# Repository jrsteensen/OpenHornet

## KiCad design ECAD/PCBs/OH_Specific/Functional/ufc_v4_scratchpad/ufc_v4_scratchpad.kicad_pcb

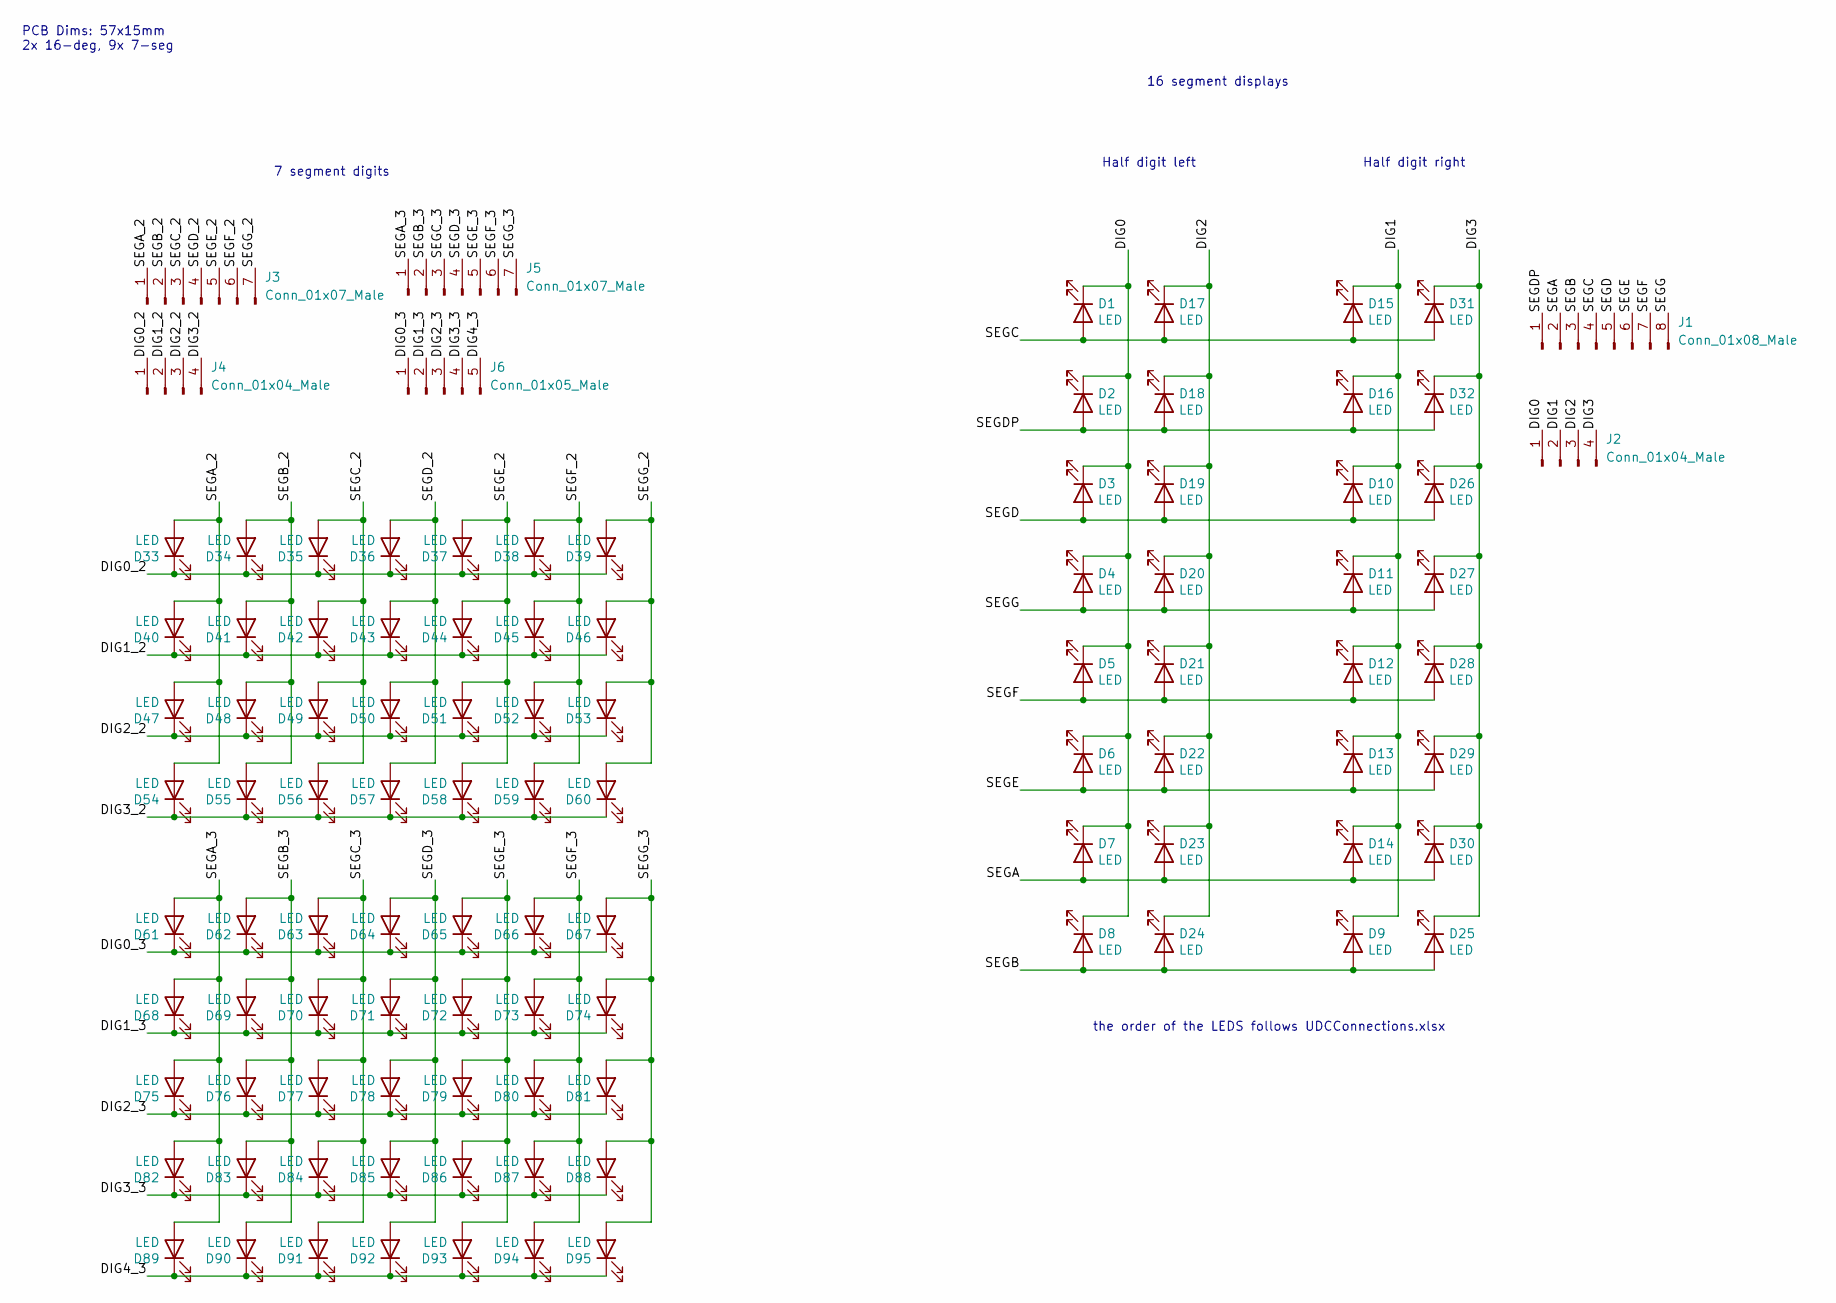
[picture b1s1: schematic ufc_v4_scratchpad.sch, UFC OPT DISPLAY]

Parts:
D1, D2, D3, D4, D5, D6, D7, D8, D9, D10, D11, D12, D13, D14, D15, D16, D17, D18, D19, D20, D21, D22, D23, D24, D25, D26, D27, D28, D29, D30, D31, D32, D33, D34, D35, D36, D37, D38, D39, D40, D41, D42, D43, D44, D45, D46, D47, D48, D49, D50, D51, D52, D53, D54, D55, D56, D57, D58, D59, D60, D61, D62, D63, D64, D65, D66, D67, D68, D69, D70, D71, D72, D73, D74, D75, D76, D77, D78, D79, D80, D81, D82, D83, D84, D85, D86, D87, D88, D89, D90, D91, D92, D93, D94, D95: LED; LED_0402_1005Metric; LCSC C130723
J1: Conn_01x08_Male; PinHeader_1x08_P1.00mm_Vertical
J2, J4: Conn_01x04_Male; PinHeader_1x04_P1.00mm_Vertical
J3, J5: Conn_01x07_Male; PinHeader_1x07_P1.00mm_Vertical
J6: Conn_01x05_Male; PinHeader_1x05_P1.00mm_Vertical

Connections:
/DIG0: D1.1 (K), D2.1 (K), D3.1 (K), D4.1 (K), D5.1 (K), D6.1 (K), D7.1 (K), D8.1 (K), J2.1
/DIG0_2: D33.1 (K), D34.1 (K), D35.1 (K), D36.1 (K), D37.1 (K), D38.1 (K), D39.1 (K), J4.1
/DIG0_3: D61.1 (K), D62.1 (K), D63.1 (K), D64.1 (K), D65.1 (K), D66.1 (K), D67.1 (K), J6.1
/DIG1: D9.1 (K), D10.1 (K), D11.1 (K), D12.1 (K), D13.1 (K), D14.1 (K), D15.1 (K), D16.1 (K), J2.2
/DIG1_2: D40.1 (K), D41.1 (K), D42.1 (K), D43.1 (K), D44.1 (K), D45.1 (K), D46.1 (K), J4.2
/DIG1_3: D68.1 (K), D69.1 (K), D70.1 (K), D71.1 (K), D72.1 (K), D73.1 (K), D74.1 (K), J6.2
/DIG2: D17.1 (K), D18.1 (K), D19.1 (K), D20.1 (K), D21.1 (K), D22.1 (K), D23.1 (K), D24.1 (K), J2.3
/DIG2_2: D47.1 (K), D48.1 (K), D49.1 (K), D50.1 (K), D51.1 (K), D52.1 (K), D53.1 (K), J4.3
/DIG2_3: D75.1 (K), D76.1 (K), D77.1 (K), D78.1 (K), D79.1 (K), D80.1 (K), D81.1 (K), J6.3
/DIG3: D25.1 (K), D26.1 (K), D27.1 (K), D28.1 (K), D29.1 (K), D30.1 (K), D31.1 (K), D32.1 (K), J2.4
/DIG3_2: D54.1 (K), D55.1 (K), D56.1 (K), D57.1 (K), D58.1 (K), D59.1 (K), D60.1 (K), J4.4
/DIG3_3: D82.1 (K), D83.1 (K), D84.1 (K), D85.1 (K), D86.1 (K), D87.1 (K), D88.1 (K), J6.4
/DIG4_3: D89.1 (K), D90.1 (K), D91.1 (K), D92.1 (K), D93.1 (K), D94.1 (K), D95.1 (K), J6.5
/SEGA: D7.2 (A), D14.2 (A), D23.2 (A), D30.2 (A), J1.2
/SEGA_2: D33.2 (A), D40.2 (A), D47.2 (A), D54.2 (A), J3.1
/SEGA_3: D61.2 (A), D68.2 (A), D75.2 (A), D82.2 (A), D89.2 (A), J5.1
/SEGB: D8.2 (A), D9.2 (A), D24.2 (A), D25.2 (A), J1.3
/SEGB_2: D34.2 (A), D41.2 (A), D48.2 (A), D55.2 (A), J3.2
/SEGB_3: D62.2 (A), D69.2 (A), D76.2 (A), D83.2 (A), D90.2 (A), J5.2
/SEGC: D1.2 (A), D15.2 (A), D17.2 (A), D31.2 (A), J1.4
/SEGC_2: D35.2 (A), D42.2 (A), D49.2 (A), D56.2 (A), J3.3
/SEGC_3: D63.2 (A), D70.2 (A), D77.2 (A), D84.2 (A), D91.2 (A), J5.3
/SEGD: D3.2 (A), D10.2 (A), D19.2 (A), D26.2 (A), J1.5
/SEGDP: D2.2 (A), D16.2 (A), D18.2 (A), D32.2 (A), J1.1
/SEGD_2: D36.2 (A), D43.2 (A), D50.2 (A), D57.2 (A), J3.4
/SEGD_3: D64.2 (A), D71.2 (A), D78.2 (A), D85.2 (A), D92.2 (A), J5.4
/SEGE: D6.2 (A), D13.2 (A), D22.2 (A), D29.2 (A), J1.6
/SEGE_2: D37.2 (A), D44.2 (A), D51.2 (A), D58.2 (A), J3.5
/SEGE_3: D65.2 (A), D72.2 (A), D79.2 (A), D86.2 (A), D93.2 (A), J5.5
/SEGF: D5.2 (A), D12.2 (A), D21.2 (A), D28.2 (A), J1.7
/SEGF_2: D38.2 (A), D45.2 (A), D52.2 (A), D59.2 (A), J3.6
/SEGF_3: D66.2 (A), D73.2 (A), D80.2 (A), D87.2 (A), D94.2 (A), J5.6
/SEGG: D4.2 (A), D11.2 (A), D20.2 (A), D27.2 (A), J1.8
/SEGG_2: D39.2 (A), D46.2 (A), D53.2 (A), D60.2 (A), J3.7
/SEGG_3: D67.2 (A), D74.2 (A), D81.2 (A), D88.2 (A), D95.2 (A), J5.7

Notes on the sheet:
PCB Dims: 57x15mm 2x 16-deg, 9x 7-seg
7 segment digits
16 segment displays
the order of the LEDS follows UDCConnections.xlsx
Half digit left
Half digit right

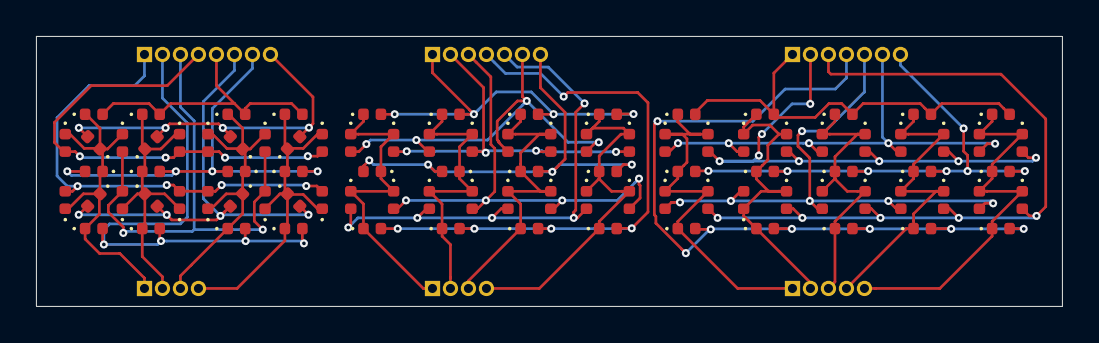
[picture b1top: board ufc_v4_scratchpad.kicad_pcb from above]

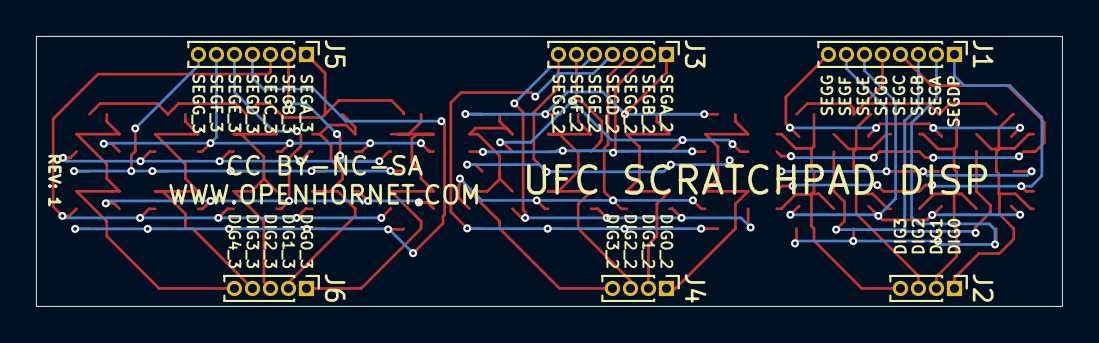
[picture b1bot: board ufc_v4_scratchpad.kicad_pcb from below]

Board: 2 copper layers, 57.0 x 15.0 mm, 101 parts (6 on the bottom side), 35 nets.

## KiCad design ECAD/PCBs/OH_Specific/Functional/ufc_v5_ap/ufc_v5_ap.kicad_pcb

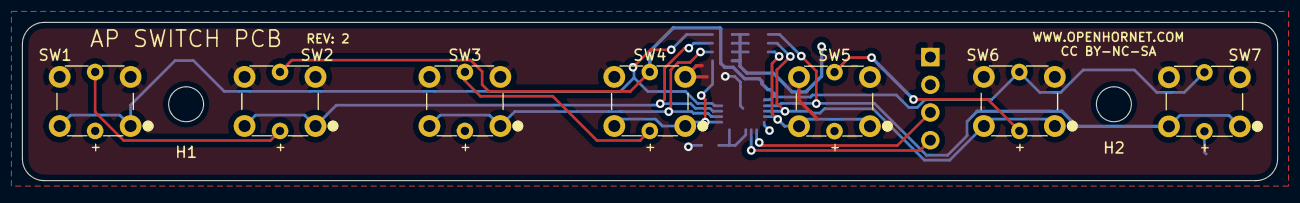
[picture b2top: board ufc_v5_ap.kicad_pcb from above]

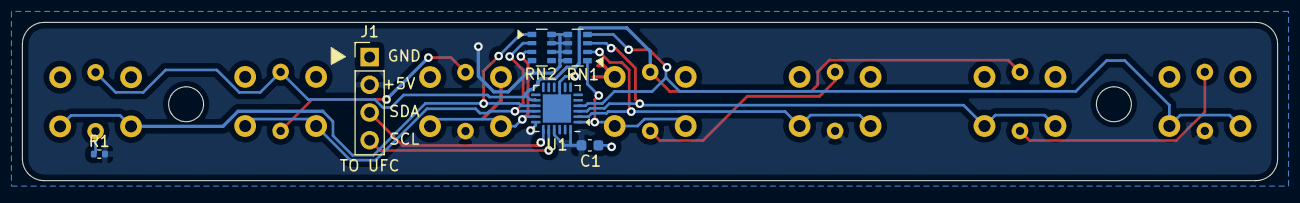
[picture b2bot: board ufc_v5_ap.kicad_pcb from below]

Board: 2 copper layers, 115.0 x 14.5 mm, 15 parts (6 on the bottom side), 16 nets.

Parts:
C1: .1uF; C_0603_1608Metric
H1, H2: MountingHole_3.2mm_M3_DIN965
J1: TO UFC; PinHeader_1x04_P2.54mm_Vertical
R1: 33; R_0402_1005Metric
RN1, RN2: 4.7K; R_Array_Convex_4x0603
SW1, SW2, SW3, SW4, SW5, SW6, SW7: TL1240GQ
U1: AW9523BTQR; WQFN-24-1EP_4x4mm_P0.5mm_EP2.6x2.6mm

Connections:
+5V: C1.1, J1.2, R1.2, RN1.5, RN1.6, RN1.7, RN1.8, RN2.6, RN2.7, RN2.8, SW1.5, SW3.5, SW5.5, U1.18, U1.21, U1.24
/AP-: SW1.6, SW2.5
/AP_SW: RN1.4, SW1.1, U1.4
/BCN+: SW5.6, SW6.5
/BCN-: SW2.6, SW4.6, SW6.6, SW7.6, U1.14
/BCN_SW: RN2.2, SW6.1, U1.16
/DL_SW: RN2.3, SW5.1, U1.17
/IFF_SW: RN1.3, SW2.1, U1.3
/ILS+: SW3.6, SW4.5
/ILS_SW: RN1.1, SW4.1, U1.1
/ON+: R1.1, SW7.5
/ON_SW: RN2.1, SW7.1, U1.15
/TCN_SW: RN1.2, SW3.1, U1.2
GND: C1.2, J1.1, SW1.2, SW2.2, SW3.2, SW4.2, SW5.2, SW6.2, SW7.2, U1.9, U1.25
SCL: J1.4, U1.20
SDA: J1.3, U1.19

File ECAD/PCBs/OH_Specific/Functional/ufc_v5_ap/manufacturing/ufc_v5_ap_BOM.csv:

Comment,Designator,Footprint,LCSC
".1uF","C1","Capacitor_SMD:C_0603_1608Metric","C14663"
"~","H1,H2","MountingHole:MountingHole_3.2mm_M3_DIN965",""
"TO UFC","J1","Connector_PinHeader_2.54mm:PinHeader_1x04_P2.54mm_Vertical",""
"33","R1","Resistor_SMD:R_0402_1005Metric","C25105"
"4.7K","RN1,RN2","Resistor_SMD:R_Array_Convex_4x0603","C1980"
"TL1240GQ","SW1,SW2,SW3,SW4,SW5,SW6,SW7","KiCAD_Libraries:TL1240GQ",""
"AW9523BTQR","U1","Package_DFN_QFN:WQFN-24-1EP_4x4mm_P0.5mm_EP2.6x2.6mm",""

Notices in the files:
ECAD/PCBs/OH_Specific/Functional/ufc_v4_scratchpad/ufc_v4_scratchpad.kicad_pcb:
CC BY-NC-SA
